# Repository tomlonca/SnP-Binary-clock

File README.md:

# SnP-Binary-Clock

This project is about designing and implementing a **binary clock** using an AtMega48 microcontroller and a custom PCB.

## Overview
The clock supports:
- **Normal mode**
- **Sleep mode**
- **Low power mode**

Mode switching is done via three buttons on the top of the board.

## Available Files
- `BinaryClock_pcb.sch` – Schematic
- `BinaryClock_pcb.prl` – PCB layout
- `BinaryClock_pcb.pcb` – Compiled firmware

## Status
Work in progress.

## Komplexaufgabe

- Bauen Sie eine Binäruhr mit dem ATmega48, benutzen Sie hierfür mindestens die ausgegebenen Bauteile
- Pflicht Features:

1. Binäre Ausgabe auf 11 LED’s mit hardware PWM Helligkeitssteuerung (OC1x-Pin).
2. Steuerung über Taster (INT0, INT1, x).
3. Sleepmode mit Beweis der Reduzierten Leistungsaufnahme nach Datenblatt.
4. Zeitbasis über Timer und Uhrenquarz, mit Genauigkeitsmessung, Programmierung über ISP.
5. Programmierung direkt über AVR-gcc kein Arduino!

- Sinnvoll wäre es, die Uhr auf der Platine aus HWP II aufzubauen!

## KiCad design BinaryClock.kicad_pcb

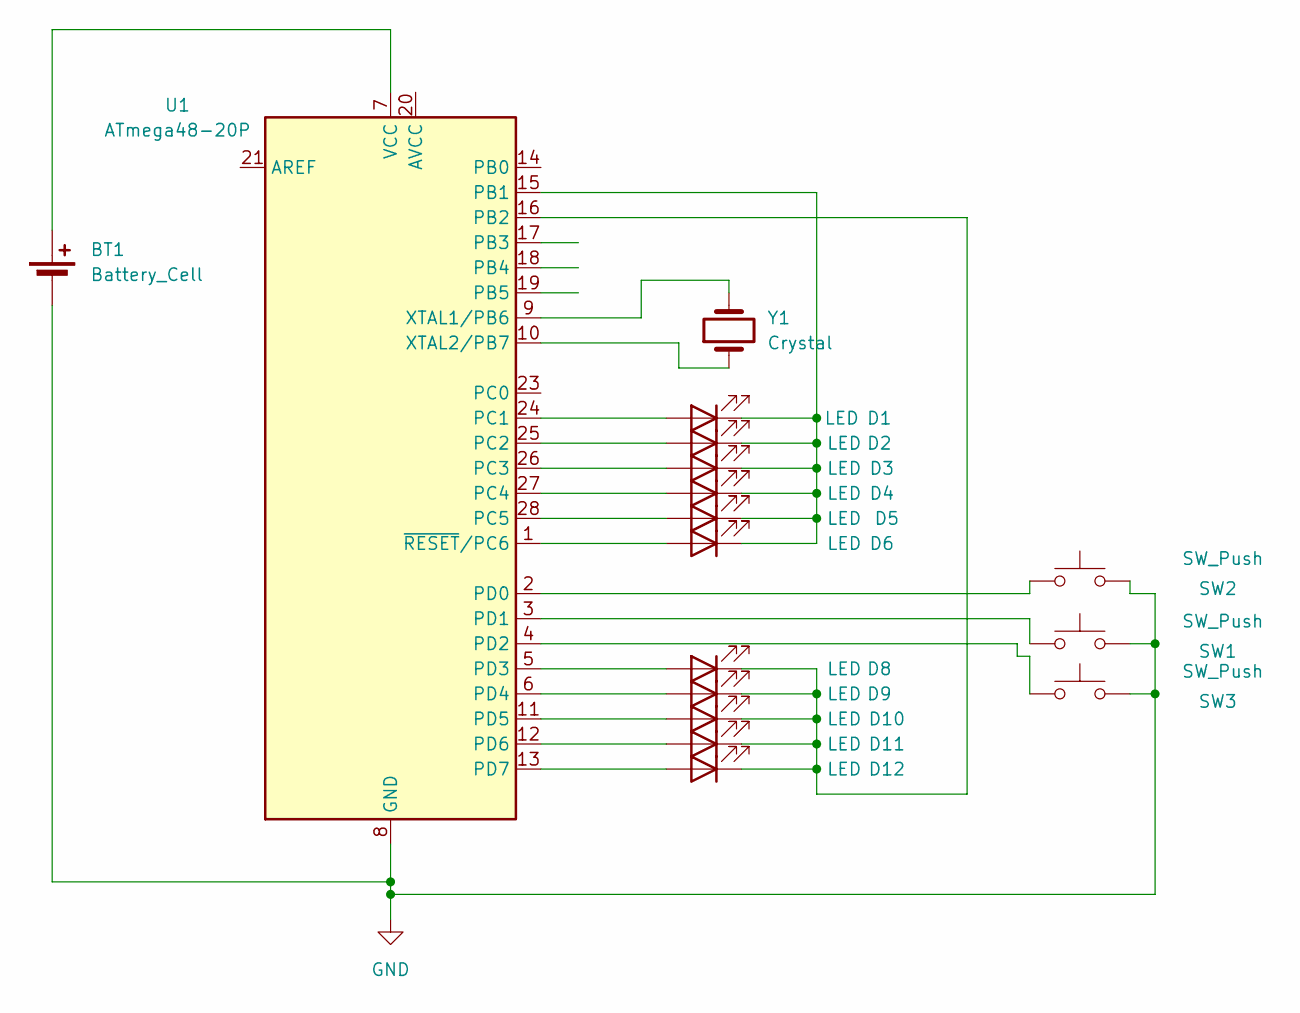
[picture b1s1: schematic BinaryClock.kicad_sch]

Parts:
BT1: Battery_Cell; BatteryHolder_Keystone_106_1x20mm
D1, D2, D3, D4, D5, D6, D8, D9, D10, D11, D12: LED; LED_D3.0mm
SW1, SW2, SW3: SW_Push; SW_TH_Tactile_Omron_B3F-10xx
U1: ATmega48-20P; CERDIP-28_W7.62mm_SideBrazed_LongPads_Socket
Y1: Crystal; Crystal_DS10_D1.0mm_L4.3mm_Vertical

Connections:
GND: BT1.2 (-), SW1.2, SW2.2, SW3.2, U1.8 (GND), U1.22 (GND)
unnamed: BT1.1 (+), U1.7 (VCC)
unnamed: D1.2 (A), U1.24 (PC1)
unnamed: D1.1 (K), D2.1 (K), D3.1 (K), D4.1 (K), D5.1 (K), D6.1 (K), U1.15 (PB1)
unnamed: D2.2 (A), U1.25 (PC2)
unnamed: D3.2 (A), U1.26 (PC3)
unnamed: D4.2 (A), U1.27 (PC4)
unnamed: D5.2 (A), U1.28 (PC5)
unnamed: D6.2 (A), U1.1 (~RESET/PC6)
unnamed: D8.2 (A), U1.5 (PD3)
unnamed: D9.2 (A), U1.6 (PD4)
unnamed: D10.2 (A), U1.11 (PD5)
unnamed: D8.1 (K), D9.1 (K), D10.1 (K), D11.1 (K), D12.1 (K), U1.16 (PB2)
unnamed: D11.2 (A), U1.12 (PD6)
unnamed: D12.2 (A), U1.13 (PD7)
unnamed: SW2.1, U1.2 (PD0)
unnamed: SW1.1, U1.3 (PD1)
unnamed: SW3.1, U1.4 (PD2)
unnamed: U1.9 (XTAL1/PB6), Y1.2
unnamed: U1.10 (XTAL2/PB7), Y1.1

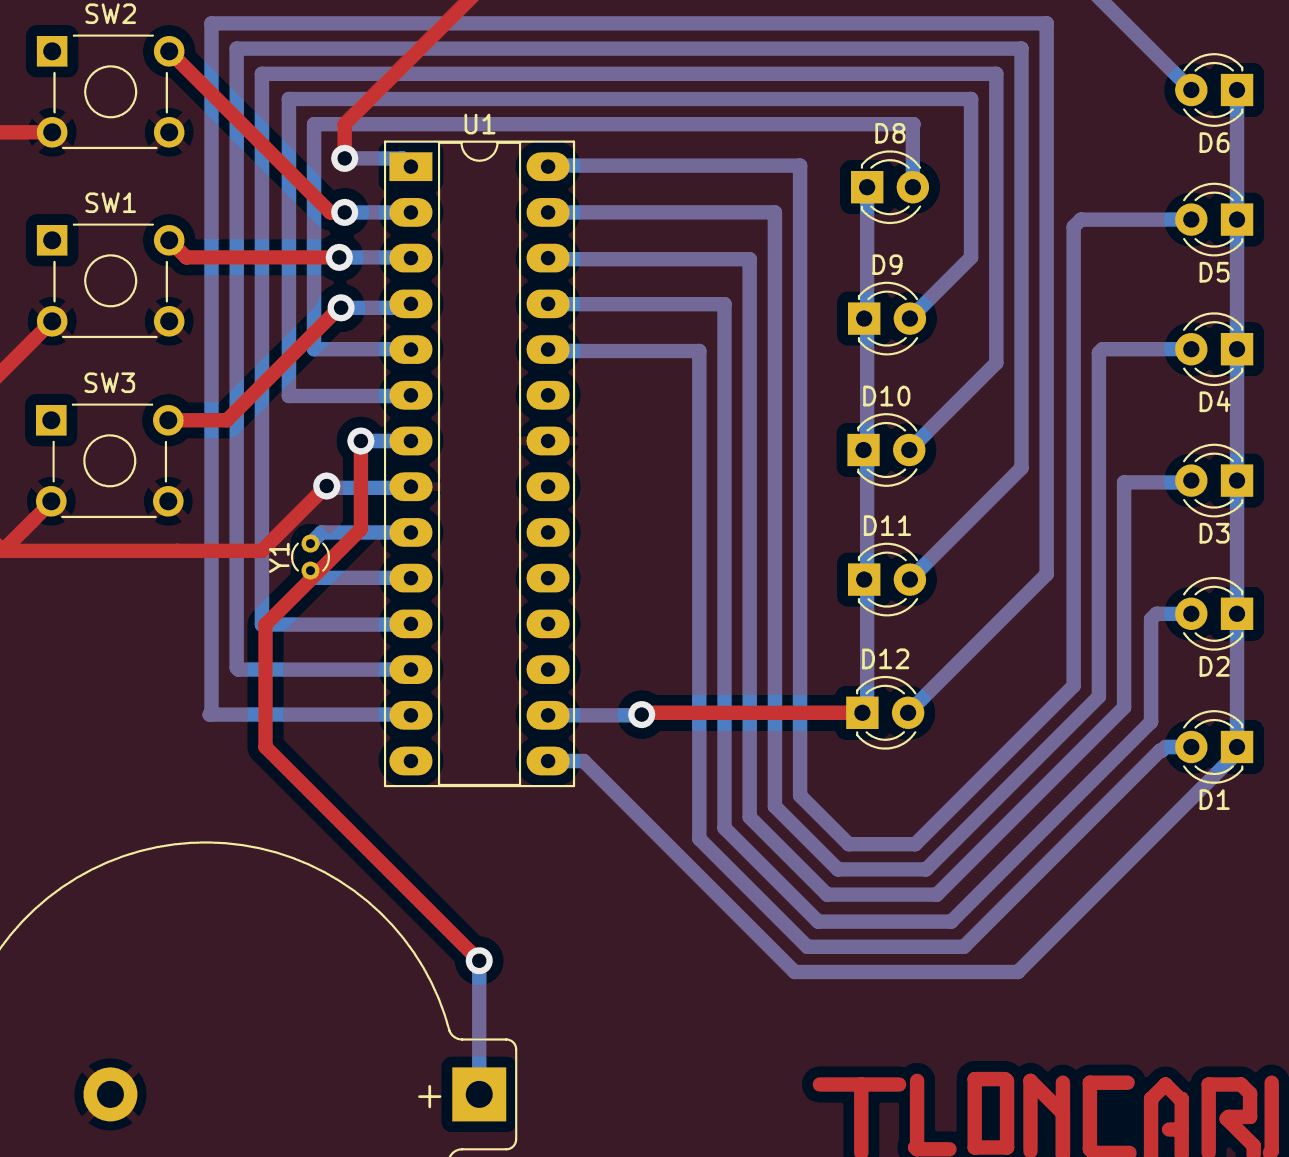
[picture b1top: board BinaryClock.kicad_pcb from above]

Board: 2 copper layers, 17 parts (0 on the bottom side), 20 nets.
